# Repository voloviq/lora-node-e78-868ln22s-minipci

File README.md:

# lora-node-e78-868ln22s-minipci
Lora Node based on E78-868LN22S module in minipci fassion

PCB View

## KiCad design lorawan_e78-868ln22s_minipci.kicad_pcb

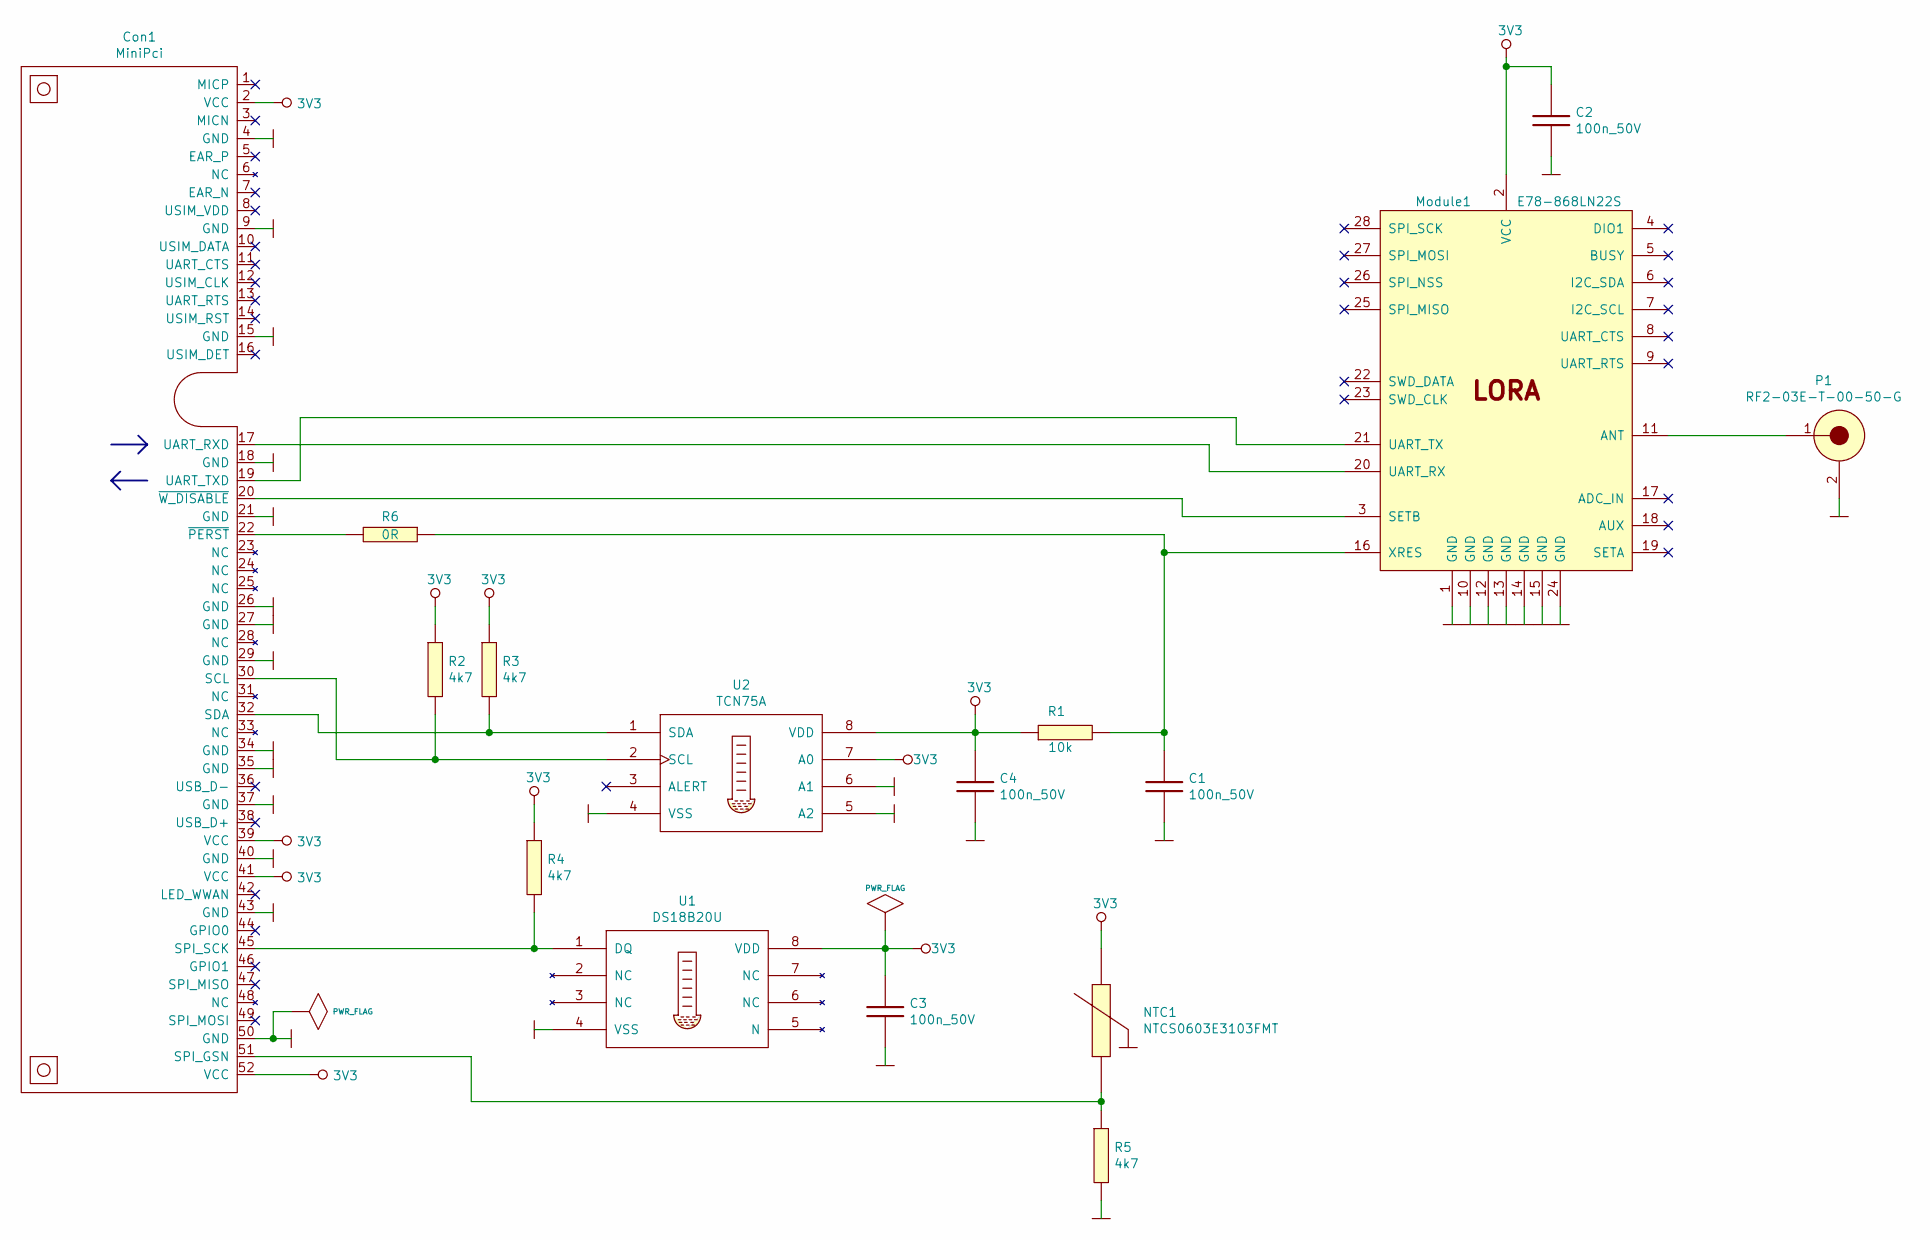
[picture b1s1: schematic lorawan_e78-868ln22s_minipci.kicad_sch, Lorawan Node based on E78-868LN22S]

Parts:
C1, C2, C3, C4: 100n_50V; 100nF_0603; Manufacturer Part Number CL10B104JB8NNNC
Con1: MiniPci; mpcie-full-card
Module1: E78-868LN22S; Manufacturer Part Number E78-868LN22S
NTC1: NTCS0603E3103FMT; Manufacturer Part Number NTCG163JF103FT1; LCSC Part # (optional) C76589
P1: RF2-03E-T-00-50-G; Manufacturer Part Number RF2-03E-T-00-50-G
R1: 10k; 10k_0603; Manufacturer Part Number 0603SAJ0103T5E
R2, R3, R4, R5: 4k7; 4k7_0603; Manufacturer Part Number 0603SAF4701T5E
R6: 0R; 0R_0603; Manufacturer Part Number 0603SAJ0000T5E; LCSC Part #(optional) C15402
U1: DS18B20U; DS18B20U_MSOP-8_3x3mm_P0.65mm
U2: TCN75A; TCN75A_SOIC8

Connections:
3V3: C2.1, C3.1, C4.1, Con1.2 (VCC), Con1.39 (VCC), Con1.41 (VCC), Con1.52 (VCC), Module1.2 (VCC), NTC1.2, R1.1, R2.1, R3.1, R4.1, U1.8 (VDD), U2.7 (A0), U2.8 (VDD)
GND: C1.2, C2.2, C3.2, C4.2, Con1.4 (GND), Con1.9 (GND), Con1.15 (GND), Con1.18 (GND), Con1.21 (GND), Con1.26 (GND), Con1.27 (GND), Con1.29 (GND), Con1.34 (GND), Con1.35 (GND), Con1.37 (GND), Con1.40 (GND), Con1.43 (GND), Con1.50 (GND), Module1.1 (GND), Module1.10 (GND), Module1.12 (GND), Module1.13 (GND), Module1.14 (GND), Module1.15 (GND), Module1.24 (GND), P1.2 (GND), R5.2, U1.4 (VSS), U2.4 (VSS), U2.5 (A2), U2.6 (A1)
unnamed: C1.1, Module1.16 (XRES), R1.2, R6.1
unnamed: Con1.17 (UART_RXD), Module1.20 (UART_RX)
unnamed: Con1.19 (UART_TXD), Module1.21 (UART_TX)
unnamed: Con1.20 (~W_DISABLE), Module1.3 (SETB)
unnamed: Con1.22 (~PERST), R6.2
unnamed: Con1.30 (SCL), R2.2, U2.2 (SCL)
unnamed: Con1.32 (SDA), R3.2, U2.1 (SDA)
unnamed: Con1.45 (SPI_SCK), R4.2, U1.1 (DQ)
unnamed: Con1.51 (SPI_GSN), NTC1.1, R5.1
unnamed: Module1.11 (ANT), P1.1 (SIGNAL)

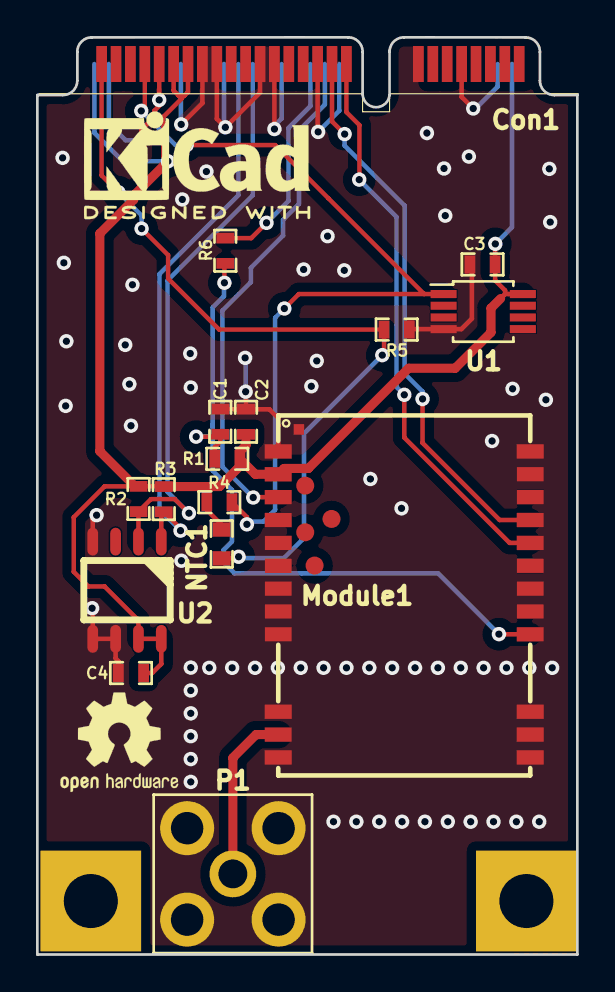
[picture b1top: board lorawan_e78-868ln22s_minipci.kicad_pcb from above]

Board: 2 copper layers, 30.0 x 51.0 mm, 17 parts (0 on the bottom side), 12 nets.

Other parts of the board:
REFe: OSHW-Logo2_7.3x6mm_SilkScreen

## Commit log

2021-01-10 Initial
2021-01-10 Added 3D View picture, updated README.md
2021-01-10 Updated 3D view picture
2021-01-21 Finalized project
2021-01-21 Finalized project, aligned BOM and position file
2021-01-21 Updated BOM
2021-02-22 Added some pcb description
2021-02-23 Modified Lora module footprint
2021-03-16 Store revision in branch v1.0
2021-03-16 Corrected project
